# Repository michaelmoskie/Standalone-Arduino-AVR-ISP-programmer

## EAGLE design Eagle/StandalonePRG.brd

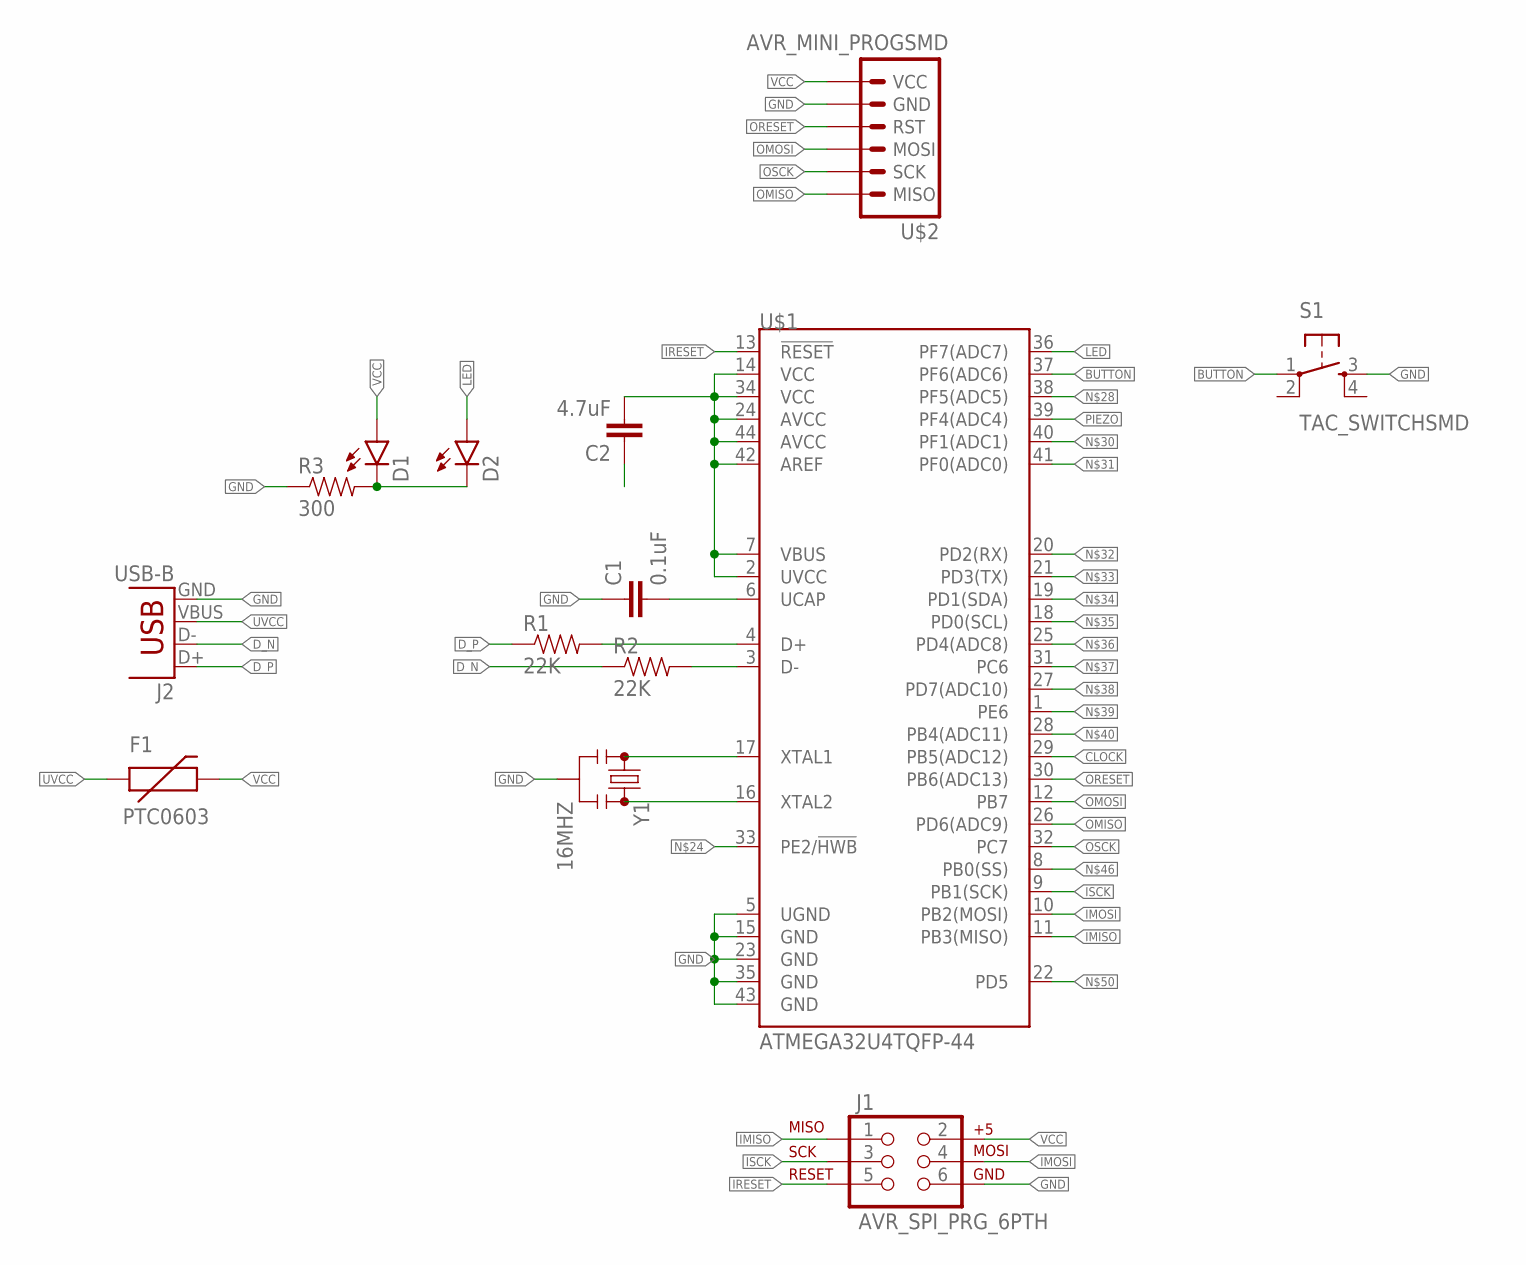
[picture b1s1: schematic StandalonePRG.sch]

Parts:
C1: 0.1uF; 0603-CAP
C2: 4.7uF; 0603-CAP
D1, D2: LED0603; LED-0603
F1: PTC0603; 0603
J1: AVR_SPI_PRG_6PTH; 2X3
J2: USB-B; USB-B-PTH
R1, R2: 22K; 0603-RES
R3: 300; 0603-RES
S1: TAC_SWITCHSMD; TACTILE-SWITCH-SMD
U$1: ATMEGA32U4TQFP-44; TQFP44
U$2: AVR_MINI_PROGSMD; AVR_MINI_PROG
Y1: 16MHZ; RESONATOR-SMD

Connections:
BUTTON: S1.1, U$1.37 (PF6(ADC6))
CLOCK: U$1.29 (PB5(ADC12))
DR_N: R2.2, U$1.3 (D-)
DR_P: R1.2, U$1.4 (D+)
D_N: J2.D-, R2.1
D_P: J2.D+, R1.1
GND: C1.1, C2.1, J1.6, J2.GND, R3.1, S1.3, U$1.5 (UGND), U$1.15 (GND), U$1.23 (GND), U$1.35 (GND), U$1.43 (GND), U$2.2 (GND), Y1.2
IMISO: J1.1, U$1.11 (PB3(MISO))
IMOSI: J1.4, U$1.10 (PB2(MOSI))
IRESET: J1.5, U$1.13 (!RESET)
ISCK: J1.3, U$1.9 (PB1(SCK))
LED: D2.A, U$1.36 (PF7(ADC7))
LGND: D1.C, D2.C, R3.2
unnamed: U$1.17 (XTAL1), Y1.1
unnamed: U$1.16 (XTAL2), Y1.3
OMISO: U$1.26 (PD6(ADC9)), U$2.6 (MISO)
OMOSI: U$1.12 (PB7), U$2.4 (MOSI)
ORESET: U$1.30 (PB6(ADC13)), U$2.3 (RST)
OSCK: U$1.32 (PC7), U$2.5 (SCK)
PIEZO: U$1.39 (PF4(ADC4))
UCAP: C1.2, U$1.6 (UCAP)
UVCC: F1.1, J2.VBUS
VCC: C2.2, D1.A, F1.2, J1.2, U$1.2 (UVCC), U$1.7 (VBUS), U$1.14 (VCC), U$1.24 (AVCC), U$1.34 (VCC), U$1.42 (AREF), U$1.44 (AVCC), U$2.1 (VCC)

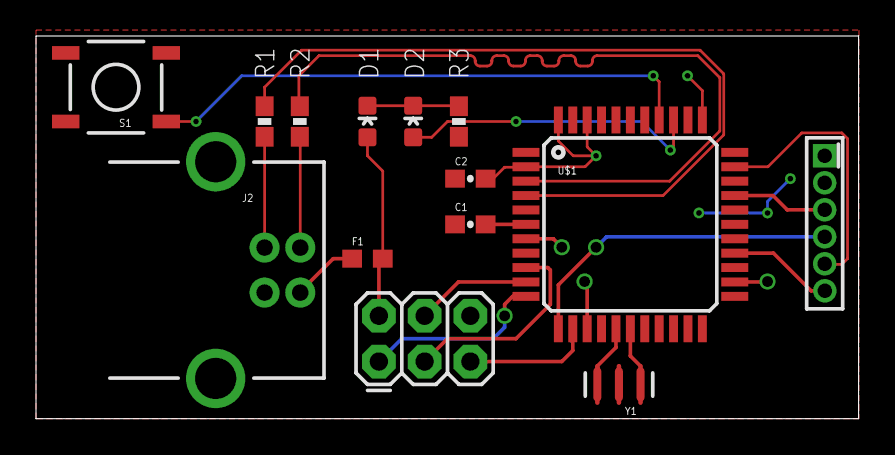
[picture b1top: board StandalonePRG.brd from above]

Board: 2 copper layers, 45.7 x 21.3 mm, 14 parts (0 on the bottom side), 21 nets.

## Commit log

2016-09-26 HexTool
    Automatically convert Intel hex files to the appropriate format for
    Adafruit’s standalone programming firmware.
2016-09-26 Support84
    Changed fuse settings for use with Attiny84 with 8MHZ internal clock.
    Changed directory structure to work with Arduino compiler.
2016-09-26 Update images.cpp
    Proper size
2016-09-26 Eagle SCH
    Basic schematic to utilize the code
2016-09-26 Example PCB

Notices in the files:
parts and their libraries:
SparkFun-Capacitors: Licensing: Creative Commons ShareAlike 4.0 International - https://creativecommons.org/licenses/by-sa/4.0
